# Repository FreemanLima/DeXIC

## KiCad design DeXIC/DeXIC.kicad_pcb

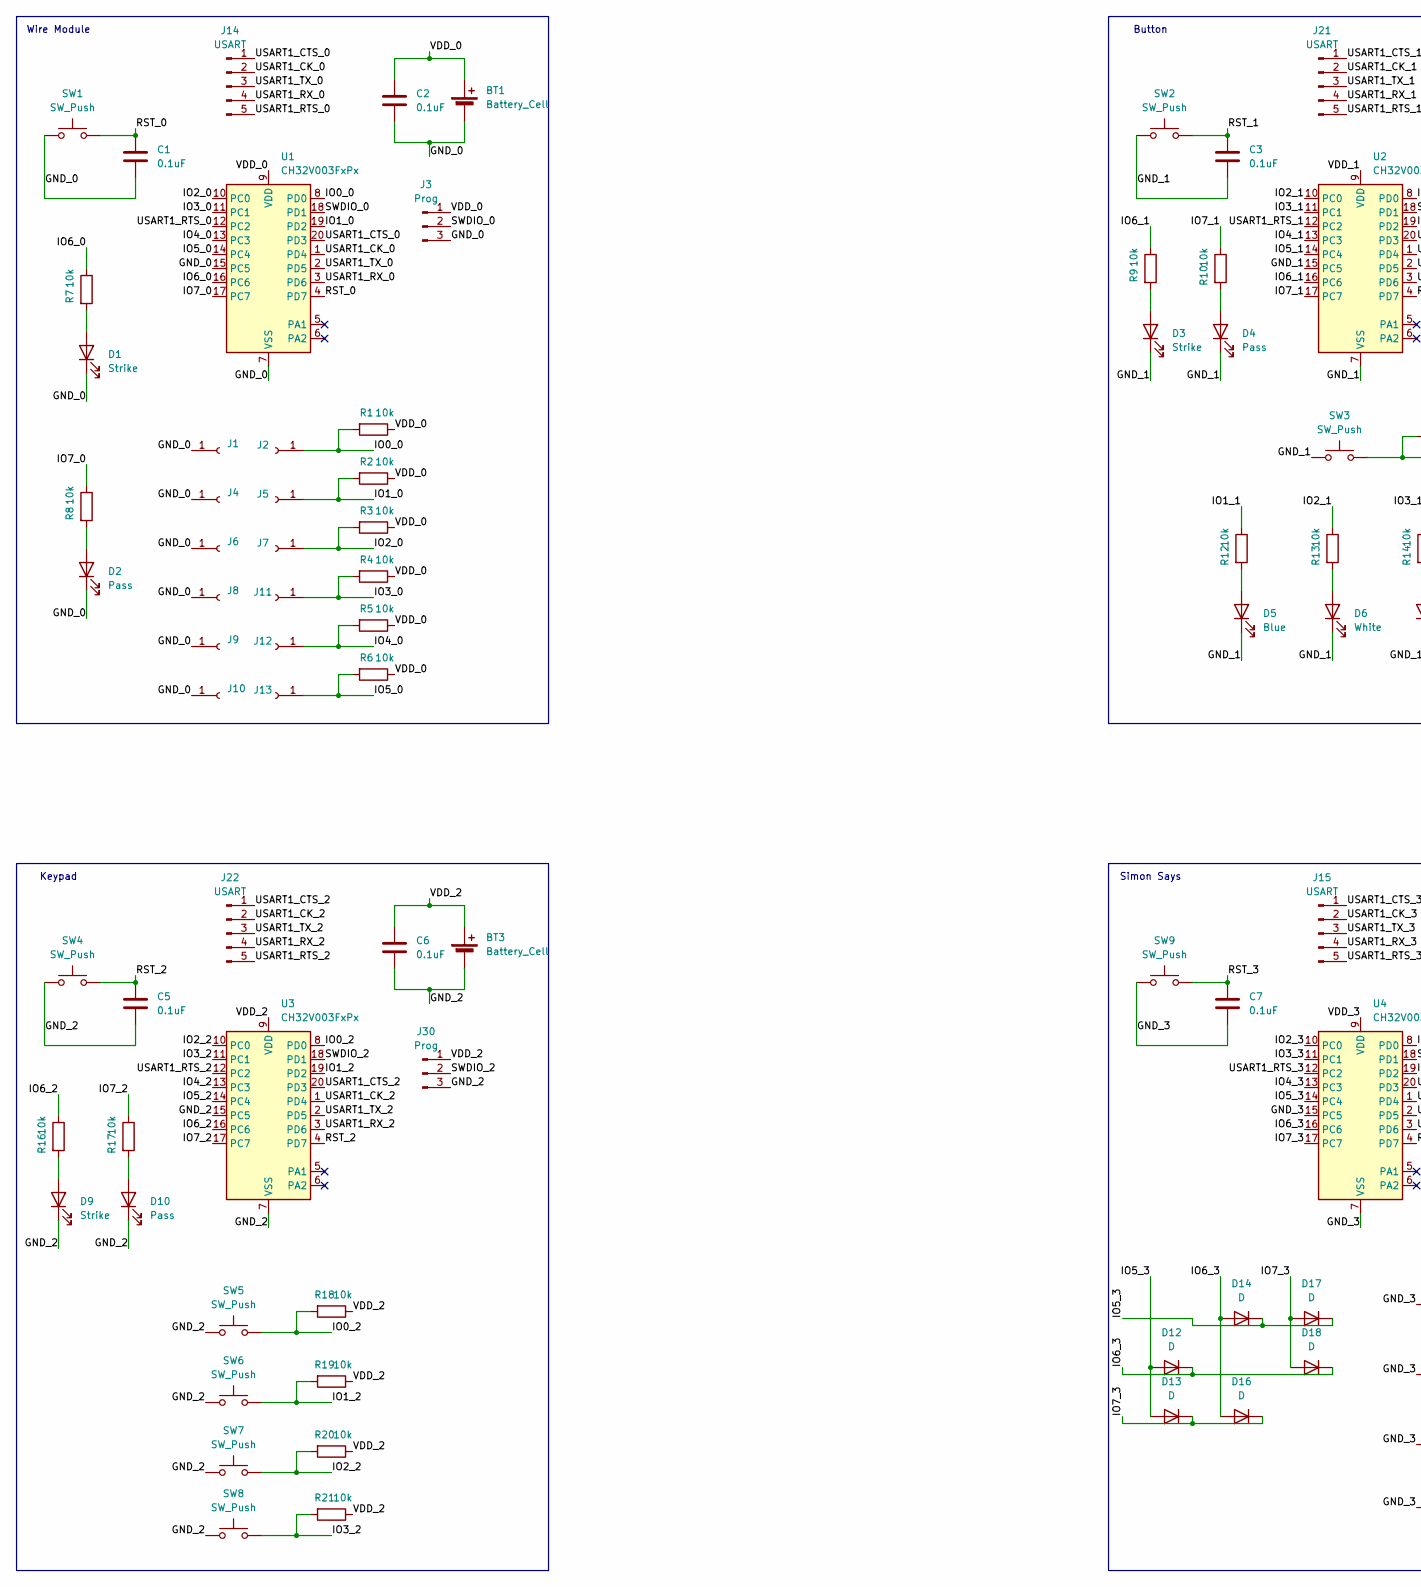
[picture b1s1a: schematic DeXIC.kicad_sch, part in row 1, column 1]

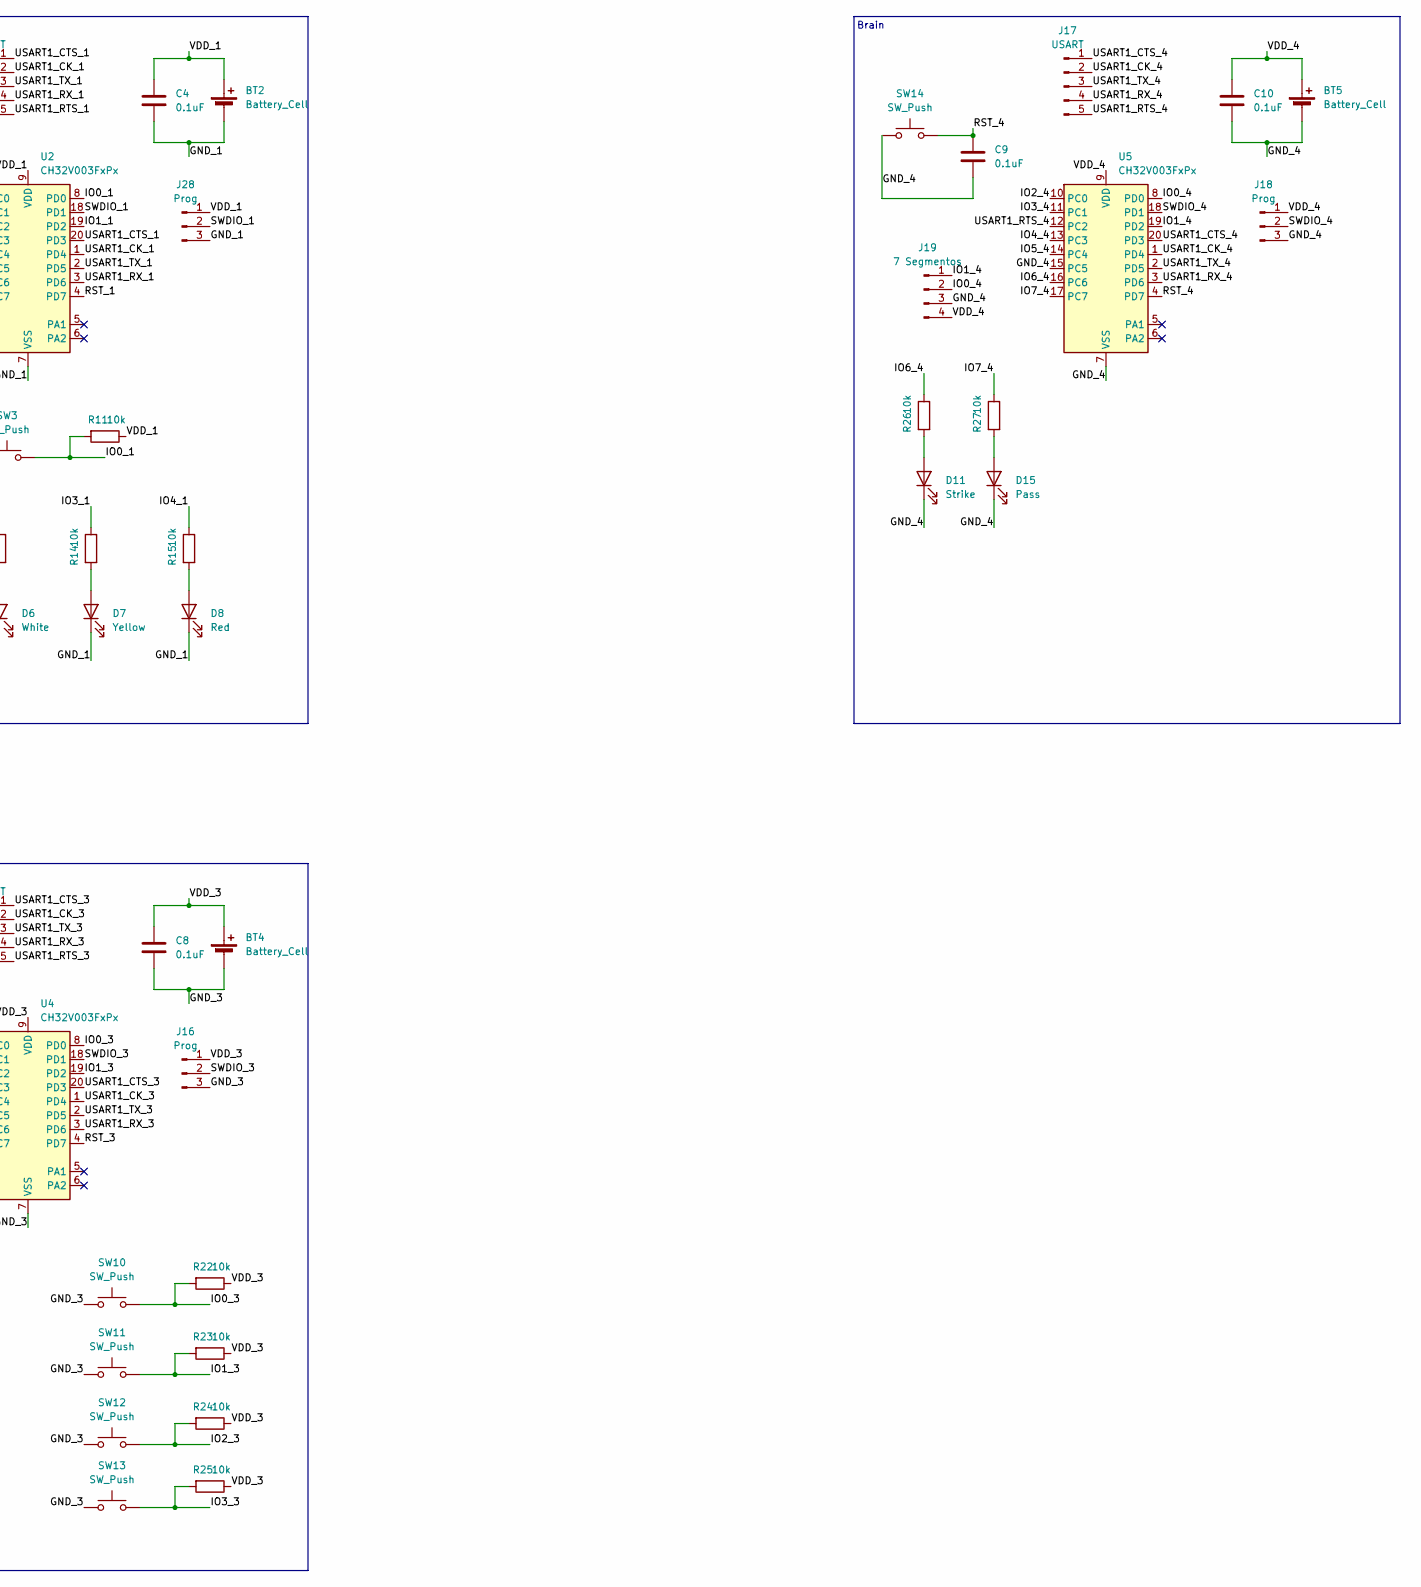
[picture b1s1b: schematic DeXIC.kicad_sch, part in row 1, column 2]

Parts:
BT1, BT2, BT3, BT4: Battery_Cell; PinHeader_2x01_P2.54mm_Vertical
BT5: Battery_Cell; BatteryHolder_Keystone_1042_1x18650
C1, C2, C3, C4, C5, C6, C7, C8, C9, C10: 0.1uF; CP_Radial_D5.0mm_P2.00mm
D1, D3, D9, D11: Strike; LED_D3.0mm
D2, D4, D10, D15: Pass; LED_D3.0mm_Clear
D5: Blue; LED_D3.0mm_Clear
D6: White; LED_D3.0mm_Clear
D7: Yellow; LED_D3.0mm_Clear
D8: Red; LED_D3.0mm
D12, D13, D14, D16, D17, D18: D; LED_D3.0mm_Clear
J1, J4, J6, J8, J9, J10: Conn_01x01_Socket; PinHeader_1x01_P2.54mm_Vertical
J2, J5, J7, J11, J12, J13: PinHeader_1x01_P2.54mm_Vertical
J3, J16, J18, J28, J30: Prog; PinHeader_1x03_P2.54mm_Vertical
J14, J15, J17, J21, J22: USART; PinHeader_1x05_P2.54mm_Vertical
J19: 7 Segmentos; PinHeader_1x04_P2.54mm_Vertical
R1, R2, R3, R4, R5, R6, R7, R8, R9, R10, R11, R12, R13, R14, R15, R16, R17, R18, R19, R20, R21, R22, R23, R24, R25, R26, R27: 10k; R_Axial_DIN0204_L3.6mm_D1.6mm_P7.62mm_Horizontal
SW1, SW2, SW3, SW4, SW5, SW6, SW7, SW8, SW9, SW10, SW11, SW12, SW13, SW14: SW_Push; SW_PUSH-12mm_Wuerth-430476085716
U1, U2, U3, U4, U5: CH32V003FxPx; TSSOP-20_4.4x6.5mm_P0.65mm

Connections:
/GND_0: BT1.2 (-), C1.2, C2.2, D1.1 (K), D2.1 (K), J1.1, J3.3, J4.1, J6.1, J8.1, J9.1, J10.1, SW1.1, U1.7 (VSS), U1.15 (PC5)
/GND_1: BT2.2 (-), C3.2, C4.2, D3.1 (K), D4.1 (K), D5.1 (K), D6.1 (K), D7.1 (K), D8.1 (K), J28.3, SW2.1, SW3.1, U2.7 (VSS), U2.15 (PC5)
/GND_2: BT3.2 (-), C5.2, C6.2, D9.1 (K), D10.1 (K), J30.3, SW4.1, SW5.1, SW6.1, SW7.1, SW8.1, U3.7 (VSS), U3.15 (PC5)
/GND_3: BT4.2 (-), C7.2, C8.2, J16.3, SW9.1, SW10.1, SW11.1, SW12.1, SW13.1, U4.7 (VSS), U4.15 (PC5)
/GND_4: BT5.2 (-), C9.2, C10.2, D11.1 (K), D15.1 (K), J18.3, J19.3, SW14.1, U5.7 (VSS), U5.15 (PC5)
/IO0_0: J2.1, R1.2, U1.8 (PD0)
/IO0_1: R11.2, SW3.2, U2.8 (PD0)
/IO0_2: R18.2, SW5.2, U3.8 (PD0)
/IO0_3: R22.2, SW10.2, U4.8 (PD0)
/IO0_4: J19.2, U5.8 (PD0)
/IO1_0: J5.1, R2.2, U1.19 (PD2)
/IO1_1: R12.1, U2.19 (PD2)
/IO1_2: R19.2, SW6.2, U3.19 (PD2)
/IO1_3: R23.2, SW11.2, U4.19 (PD2)
/IO1_4: J19.1, U5.19 (PD2)
/IO2_0: J7.1, R3.2, U1.10 (PC0)
/IO2_1: R13.1, U2.10 (PC0)
/IO2_2: R20.2, SW7.2, U3.10 (PC0)
/IO2_3: R24.2, SW12.2, U4.10 (PC0)
/IO2_4: U5.10 (PC0)
/IO3_0: J11.1, R4.2, U1.11 (PC1)
/IO3_1: R14.1, U2.11 (PC1)
/IO3_2: R21.2, SW8.2, U3.11 (PC1)
/IO3_3: R25.2, SW13.2, U4.11 (PC1)
/IO3_4: U5.11 (PC1)
/IO4_0: J12.1, R5.2, U1.13 (PC3)
/IO4_1: R15.1, U2.13 (PC3)
/IO4_2: U3.13 (PC3)
/IO4_3: U4.13 (PC3)
/IO4_4: U5.13 (PC3)
/IO5_0: J13.1, R6.2, U1.14 (PC4)
/IO5_1: U2.14 (PC4)
/IO5_2: U3.14 (PC4)
/IO5_3: D12.2 (A), D13.2 (A), D14.1 (K), D17.1 (K), U4.14 (PC4)
/IO5_4: U5.14 (PC4)
/IO6_0: R7.1, U1.16 (PC6)
/IO6_1: R9.1, U2.16 (PC6)
/IO6_2: R16.1, U3.16 (PC6)
/IO6_3: D12.1 (K), D14.2 (A), D16.2 (A), D18.1 (K), U4.16 (PC6)
/IO6_4: R26.1, U5.16 (PC6)
/IO7_0: R8.1, U1.17 (PC7)
/IO7_1: R10.1, U2.17 (PC7)
/IO7_2: R17.1, U3.17 (PC7)
/IO7_3: D13.1 (K), D16.1 (K), D17.2 (A), D18.2 (A), U4.17 (PC7)
/IO7_4: R27.1, U5.17 (PC7)
/RST_0: C1.1, SW1.2, U1.4 (PD7)
/RST_1: C3.1, SW2.2, U2.4 (PD7)
/RST_2: C5.1, SW4.2, U3.4 (PD7)
/RST_3: C7.1, SW9.2, U4.4 (PD7)
/RST_4: C9.1, SW14.2, U5.4 (PD7)
/SWDIO_0: J3.2, U1.18 (PD1)
/SWDIO_1: J28.2, U2.18 (PD1)
/SWDIO_2: J30.2, U3.18 (PD1)
/SWDIO_3: J16.2, U4.18 (PD1)
/SWDIO_4: J18.2, U5.18 (PD1)
/USART1_CK_0: J14.2, U1.1 (PD4)
/USART1_CK_1: J21.2, U2.1 (PD4)
/USART1_CK_2: J22.2, U3.1 (PD4)
/USART1_CK_3: J15.2, U4.1 (PD4)
/USART1_CK_4: J17.2, U5.1 (PD4)
/USART1_CTS_0: J14.1, U1.20 (PD3)
/USART1_CTS_1: J21.1, U2.20 (PD3)
/USART1_CTS_2: J22.1, U3.20 (PD3)
/USART1_CTS_3: J15.1, U4.20 (PD3)
/USART1_CTS_4: J17.1, U5.20 (PD3)
/USART1_RTS_0: J14.5, U1.12 (PC2)
/USART1_RTS_1: J21.5, U2.12 (PC2)
/USART1_RTS_2: J22.5, U3.12 (PC2)
/USART1_RTS_3: J15.5, U4.12 (PC2)
/USART1_RTS_4: J17.5, U5.12 (PC2)
/USART1_RX_0: J14.4, U1.3 (PD6)
/USART1_RX_1: J21.4, U2.3 (PD6)
/USART1_RX_2: J22.4, U3.3 (PD6)
/USART1_RX_3: J15.4, U4.3 (PD6)
/USART1_RX_4: J17.4, U5.3 (PD6)
/USART1_TX_0: J14.3, U1.2 (PD5)
/USART1_TX_1: J21.3, U2.2 (PD5)
/USART1_TX_2: J22.3, U3.2 (PD5)
/USART1_TX_3: J15.3, U4.2 (PD5)
/USART1_TX_4: J17.3, U5.2 (PD5)
/VDD_0: BT1.1 (+), C2.1, J3.1, R1.1, R2.1, R3.1, R4.1, R5.1, R6.1, U1.9 (VDD)
/VDD_1: BT2.1 (+), C4.1, J28.1, R11.1, U2.9 (VDD)
/VDD_2: BT3.1 (+), C6.1, J30.1, R18.1, R19.1, R20.1, R21.1, U3.9 (VDD)
/VDD_3: BT4.1 (+), C8.1, J16.1, R22.1, R23.1, R24.1, R25.1, U4.9 (VDD)
/VDD_4: BT5.1 (+), C10.1, J18.1, J19.4, U5.9 (VDD)
unnamed: D1.2 (A), R7.2
unnamed: D2.2 (A), R8.2
unnamed: D3.2 (A), R9.2
unnamed: D4.2 (A), R10.2
unnamed: D5.2 (A), R12.2
unnamed: D6.2 (A), R13.2
unnamed: D7.2 (A), R14.2
unnamed: D8.2 (A), R15.2
unnamed: D9.2 (A), R16.2
unnamed: D10.2 (A), R17.2
unnamed: D11.2 (A), R26.2
unnamed: D15.2 (A), R27.2

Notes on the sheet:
Simon Says
Brain
Button
Keypad
Wire Module

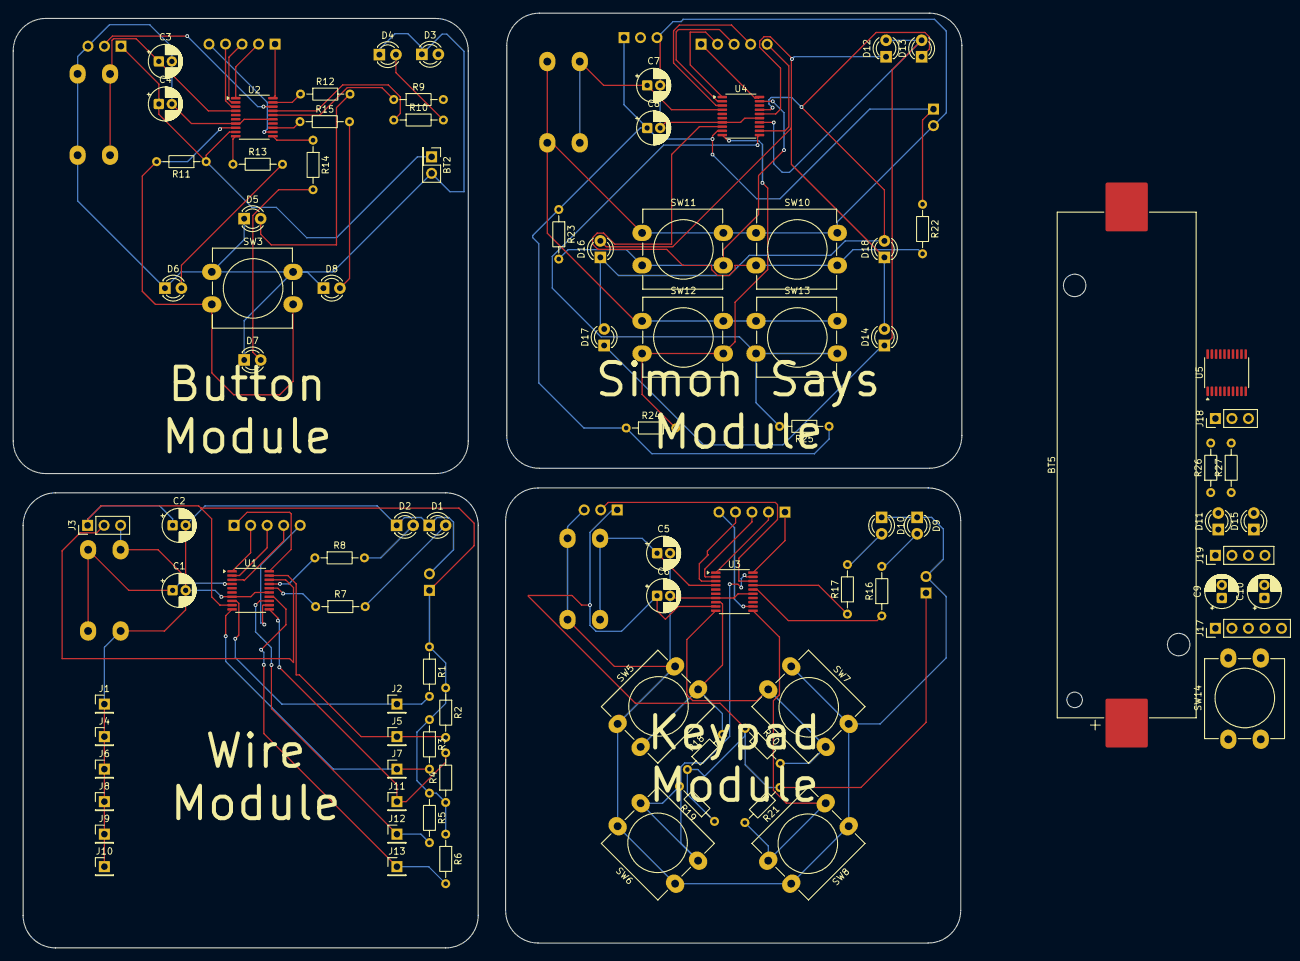
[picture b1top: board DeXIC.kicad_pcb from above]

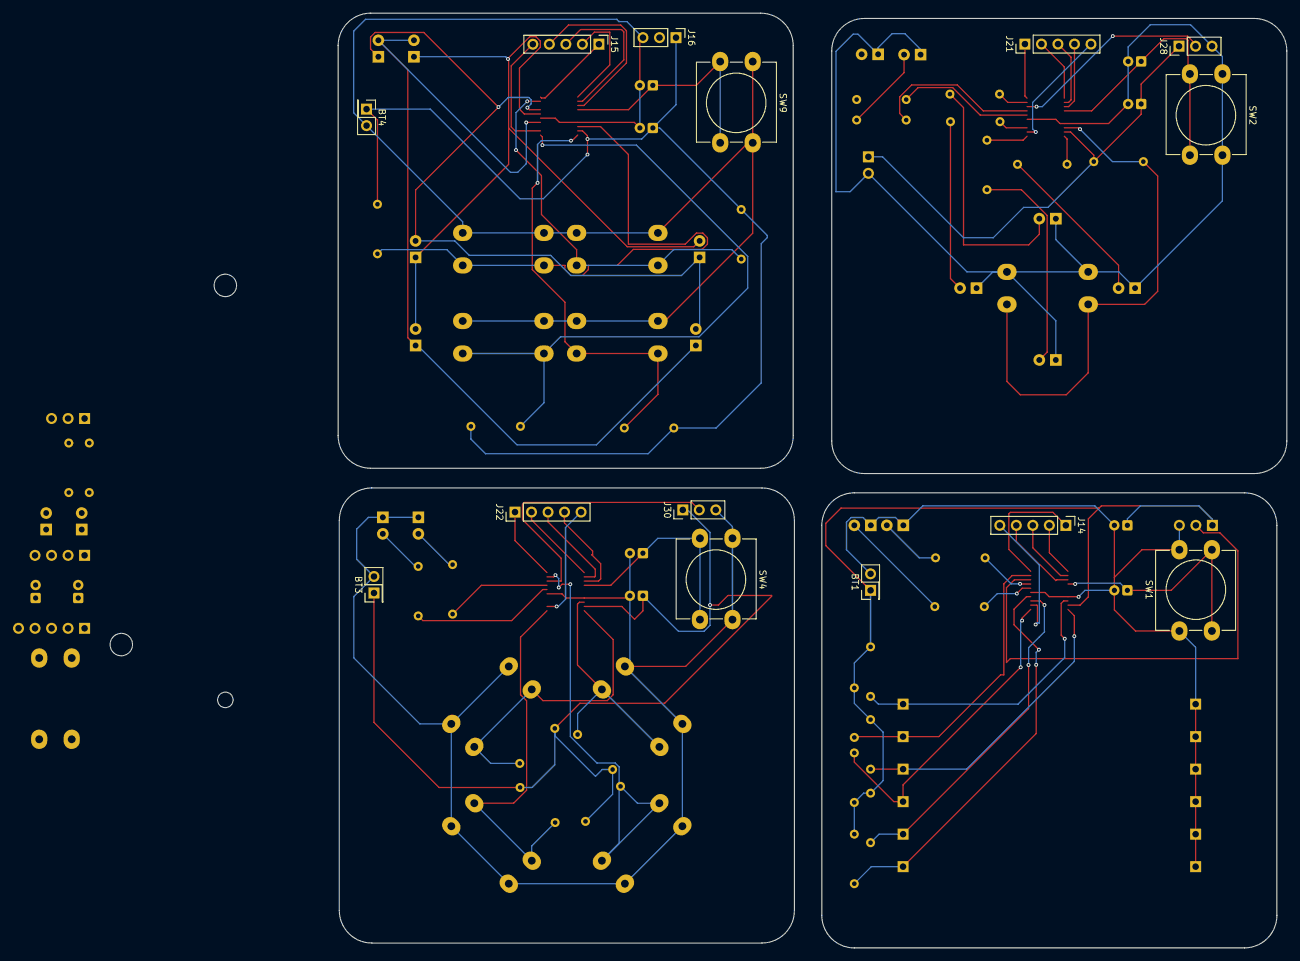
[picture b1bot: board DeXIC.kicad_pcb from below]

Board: 2 copper layers, 145.9 x 143.8 mm, 102 parts (14 on the bottom side), 89 nets.

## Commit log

2025-12-11 Kicad Innit
2025-12-11 first
2025-12-11 Next
2025-12-12 Blashhh
2025-12-12 Final
2025-12-13 last
